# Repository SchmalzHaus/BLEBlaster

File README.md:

# BLEBlaster
Arduino/chipKIT OSHW shield with RN4678 BLE module from Microchip (plus 4 high power FETs)

Currently this repo is just a place for people to share the latest versions of the BLE Blaster files.

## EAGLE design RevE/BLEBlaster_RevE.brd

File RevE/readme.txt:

Guide for BLE Blaster Rev E shield

Please see the BLE Blaster Rev E Guide PDF file to see where each of the following features lies on the board.

SW Switch:

The SW Switch, which was a simple push button in the schematic and BOM, has been replaced on the boards with a slide switch. When the switch is pushed to the right (towards the BLE module) the module will be awake. When it is pushed to the left (away from the BLE module) it will be asleep.

High Powered FETs:

There are four high power FETs on the left hand side of the board. They take power from the FET Power Input screw terminals, and switch the positive power input to GND. Eaceh of the four output screw terminal blocks has to output terminals - a positive (unswiched) and a return (switched). The positive terminals are all connected together, and are also connected to the FET Power Input + input terminal. The terminals labeled 5, 6, 9, and 10 (on the silk screen) are switched to GND by the FETs, and are controlled by Arduino digital pins with the number given by the label. All of these pins are hardware PWM outputs on both Arduinos and chipKITs, so you can use this to do LED dimming or motor speed control, etc. There are through hole spots for BEMF diodes (D9, D9, D10 and D11) to be soldered in, but they are not populated by default. They would be used if any of the FET outputs had an inductive load like a relay or motor attached. 

Prototyping Area:

There are a few holes for prototyping circuits. There are some GND, 5V (if available), and 3.3V holes allong the bottom edge of the prototyping area.

3.3V Power LED (Green):

When lit, this LED indicates the presense of 3.3V on the board.

Connection LED (Red):

This LED is controlled by the BLE module, and has different meanings depending on the mode the BLE module is in. See BLE module datasheet for more information.

UART Connector:

This connector contains GND, 3.3V, TX, RX, CTS and RTS, and is pinned out for the MCP2200 module. It allows a direction connection to the BLE module should you want to communicate with it directly from a PC rather than going through a chipKIT or Arduino board.

Wakeup Button, Reset Button:

These are push buttons used by the BLE module. See the BLE module datasheet for more information.

System Mode Selection Jumpers:

This is a block of 9 pins. The left hand colum of 3 pins is all connected to +3.3V, the right hand column to GND, and the center column is connected to the P2_0, P2_4, and EAN pins of the BLE module. You would place jumpers across these pins to set the logic levels of thes three BLE module pins on boot to enter special firmware programming modes, for example. Note that no jumpers need to be connected to run normally, as the BLE module handles pull ups/pull downs appropriately for these three I/O pins.

Reset Enable Jumper:

Normally this jumper is not connected. But if you want to control the BLE module's reset pin from an Arduino/chipKIT pin (A5) then connect this jumper.

Voltage Select Jjumper:

This jumper needs to be connected. The left two pins should be shorted together if a 3.3V Arduino/chipKIT board is used, and the right to pins should be shorted if a 5V board is used. This simply sets the high-side voltage level of the level converters for TX, RX, P1_5 and P0_4.

I/O Enable Jumpers:

This is a block of 6 pairs of pins. Each of the 6 pins on the left (8, SDA, SCL, 7, 4, 13) can be shorted across to the pins on the right (WKUP, P1_3, P1_2, P0_4, P1_5 and SW_BTN) if so desired. The left hand column are Arduino/chipKIT pin names, and the right hand column are BLE module pin names. This jumper block allows any of the available BLE module pins to be connected to Arduino/chipKIT pins. None of these jumpers need to be connected by default - they are all optional.

RX Jumpers/TX Jumpers:

Each of these is a block of 4 sets of pins. On the left of each block are four different Arduino/chipKIT digital I/O pins, and the right hand column is all connected together, and goes to either the RX or TX level shifters and then on to the BLE module. These blocks are where you select which UART (or set of pins on the Arduino/chipKIT interface) the BLE modules connects to. For example, if you want the BLE module to connect to the standard Arduino hardware serial on pins 0 and 1, then you would put shorting jumpers across the bottom two pins of each of the blocks. You can move the jumpers up or down the blocks to select different TX or RX connections from the BLE module to the Arduino/chipKIT board. This allows for maximum flexibility when using the BLE Blaster shield, as you can avoid using UARTs that are already used for other purposes on your project.

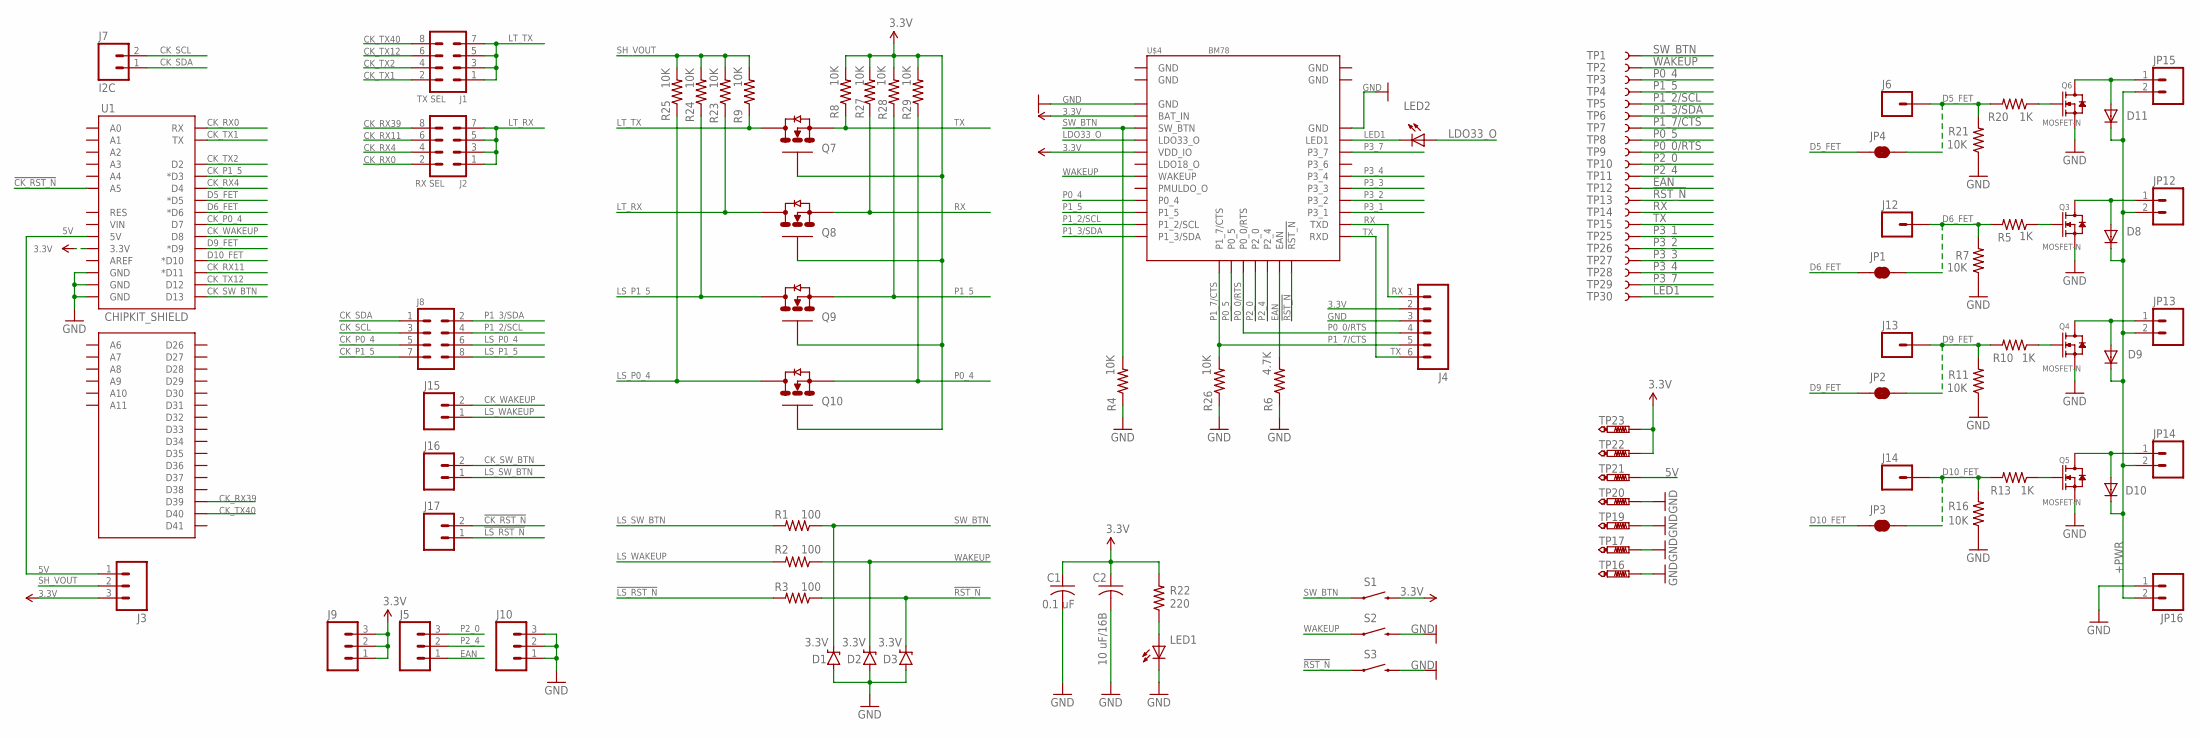
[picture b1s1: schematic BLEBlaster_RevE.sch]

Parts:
C1: 0.1 uF; C0603
C2: 10 uF/16B; C0805K
D1, D2, D3: 3.3V; SOD-323
D8, D9, D10, D11: DIODE-D-2.5; D-2.5
J1: TX SEL; 2X4
J2: RX SEL; 2X4
J3: M03PTH; 1X03
J4: M06SILK_FEMALE_PTH; 1X06
J5, J9, J10: M031X03_NO_SILK; 1X03_NO_SILK
J6, J12, J13, J14: M01PTH; 1X01
J7: I2C; 1X02_NO_SILK
J8: M04X2; 2X4
J15, J16, J17: M02PTH; 1X02
JP1, JP2, JP3, JP4: JUMPER-PAD-2-NC_BY_TRACE; PAD-JUMPER-2-NC_BY_TRACE_YES_SILK
JP12, JP13, JP14, JP15, JP16: M023.5MM; SCREWTERMINAL-3.5MM-2
LED1, LED2: LEDCHIPLED_0603; CHIPLED_0603
Q3, Q4, Q5, Q6: MOSFET-N; SOT-23
Q7, Q8, Q9, Q10: BSS138; SOT23
R1, R2, R3: 100; R0603
R4, R7, R8, R9, R11, R16, R21, R23, R24, R25, R26, R27, R28, R29: 10K; R0603
R5, R10, R13, R20: 1K; R0603
R6: 4.7K; R0603
R22: 220; R0603
S1, S2, S3: SWITCH-MOMENTARY-2SMD-4.6X2.8MM; TACTILE_SWITCH_SMD_4.6X2.8MM
TP1, TP2, TP3, TP4, TP5, TP6, TP7, TP8, TP9, TP10, TP11, TP12, TP13, TP14, TP15, TP25, TP26, TP27, TP28, TP29, TP30: TEST-POINT3X5; PAD.03X.05
TP16: 2 Pin Male Header, shared with TP24; P1-13
TP17, TP19, TP20, TP21, TP22, TP23: DNP; P1-13
U1: CHIPKIT_SHIELD; CHIPKIT_SHIELD_NOSILK
U$1: CHIPKIT2MM; CHIPKIT_2MM
U$2: ROHS_GARBAGE; ROHS_GARBAGE_5MM
U$3: CE_MARK5MM; CE_5MM
U$4: BM78; BM78SPPS5MC2/NC2

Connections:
3.3V: C1.1, C2.1, J3.3, J4.2, J9.1, J9.2, J9.3, Q7.1 (G), Q8.1 (G), Q9.1 (G), Q10.1 (G), R8.2, R22.2, R27.2, R28.2, R29.2, S1.3 (2), S1.4 (2), TP22.TP, TP23.TP, U1.3.3V, U$4.P4 (BAT_IN), U$4.P7 (VDD_IO)
5V: J3.1, TP21.TP, U1.5V
!CK_RST_N!: J17.2, U1.A5
!LS_RST_N!: J17.1, R3.2
!RST_N!: D3.C, R3.1, S3.1, S3.2 (1), TP13.P$1, U$4.P21 (!RST_N!)
+PWR: D8.C, D9.C, D10.C, D11.C, JP12.2, JP13.2, JP14.2, JP15.2, JP16.2
CK_P0_4: J8.5, U1.D7
CK_P1_5: J8.7, U1.D3 (*D3)
CK_RX0: J2.2, U1.RX
CK_RX4: J2.4, U1.D4
CK_RX11: J2.6, U1.D11 (*D11)
CK_RX39: J2.8, U1.D39
CK_SCL: J7.2, J8.3
CK_SDA: J7.1, J8.1
CK_SW_BTN: J16.2, U1.D13
CK_TX1: J1.2, U1.TX
CK_TX2: J1.4, U1.D2
CK_TX12: J1.6, U1.D12
CK_TX40: J1.8, U1.D40
CK_WAKEUP: J15.2, U1.D8
D5_FET: JP4.1, U1.D5 (*D5)
D5_FET_: J6.1, JP4.2, R20.2, R21.2
D6_FET: JP1.1, U1.D6 (*D6)
D6_FET_: J12.1, JP1.2, R5.2, R7.2
D9_FET: JP2.1, U1.D9 (*D9)
D9_FET_: J13.1, JP2.2, R10.2, R11.2
D10_FET: JP3.1, U1.D10 (*D10)
D10_FET_: J14.1, JP3.2, R13.2, R16.2
EAN: J5.1, R6.2, TP12.P$1, U$4.P20 (EAN)
GND: C1.2, C2.2, D1.A, D2.A, D3.A, J4.3, J10.1, J10.2, J10.3, JP16.1, LED1.C, Q3.2 (S), Q4.2 (S), Q5.2 (S), Q6.2 (S), R4.1, R6.1, R7.1, R11.1, R16.1, R21.1, R26.1, S2.3 (2), S2.4 (2), S3.3 (2), S3.4 (2), TP16.TP, TP17.TP, TP19.TP, TP20.TP, U1.GND@0 (GND), U1.GND@1 (GND), U1.GND@2 (GND), U$4.P1 (GND), U$4.P2 (GND), U$4.P3 (GND), U$4.P31 (GND), U$4.P32 (GND), U$4.P33 (GND)
LDO18_O: U$4.P8 (LDO18_O)
LDO33_O: LED2.A, U$4.P6 (LDO33_O)
LED1: LED2.C, TP30.P$1, U$4.P30 (LED1)
LS_P0_4: J8.6, Q10.3 (D), R25.1
LS_P1_5: J8.8, Q9.3 (D), R24.1
LS_SW_BTN: J16.1, R1.2
LS_WAKEUP: J15.1, R2.2
LT_RX: J2.1, J2.3, J2.5, J2.7, Q8.3 (D), R23.1
LT_TX: J1.1, J1.3, J1.5, J1.7, Q7.3 (D), R9.1
unnamed: Q3.1 (G), R5.1
unnamed: Q4.1 (G), R10.1
unnamed: Q5.1 (G), R13.1
unnamed: Q6.1 (G), R20.1
unnamed: D11.A, JP15.1, Q6.3 (D)
unnamed: D10.A, JP14.1, Q5.3 (D)
unnamed: LED1.A, R22.1
unnamed: D9.A, JP13.1, Q4.3 (D)
unnamed: D8.A, JP12.1, Q3.3 (D)
P0_0/RTS: J4.4, TP9.P$1, U$4.P17 (P0_0/RTS)
P0_4: Q10.2 (S), R29.1, TP3.P$1, U$4.P11 (P0_4)
P0_5: TP8.P$1, U$4.P16 (P0_5)
P1_2/SCL: J8.4, TP5.P$1, U$4.P13 (P1_2/SCL)
P1_3/SDA: J8.2, TP6.P$1, U$4.P14 (P1_3/SDA)
P1_5: Q9.2 (S), R28.1, TP4.P$1, U$4.P12 (P1_5)
P1_7/CTS: J4.5, R26.2, TP7.P$1, U$4.P15 (P1_7/CTS)
P2_0: J5.3, TP10.P$1, U$4.P18 (P2_0)
P2_4: J5.2, TP11.P$1, U$4.P19 (P2_4)
P3_1: TP25.P$1, U$4.P24 (P3_1)
P3_2: TP26.P$1, U$4.P25 (P3_2)
P3_3: TP27.P$1, U$4.P26 (P3_3)
P3_4: TP28.P$1, U$4.P27 (P3_4)
P3_7: TP29.P$1, U$4.P29 (P3_7)
PMULDO_O: U$4.P10 (PMULDO_O)
RX: J4.1, Q8.2 (S), R27.1, TP14.P$1, U$4.P23 (TXD)
SH_VOUT: J3.2, R9.2, R23.2, R24.2, R25.2
SW_BTN: D1.C, R1.1, R4.2, S1.1, S1.2 (1), TP1.P$1, U$4.P5 (SW_BTN)
TX: J4.6, Q7.2 (S), R8.1, TP15.P$1, U$4.P22 (RXD)
WAKEUP: D2.C, R2.1, S2.1, S2.2 (1), TP2.P$1, U$4.P9 (WAKEUP)

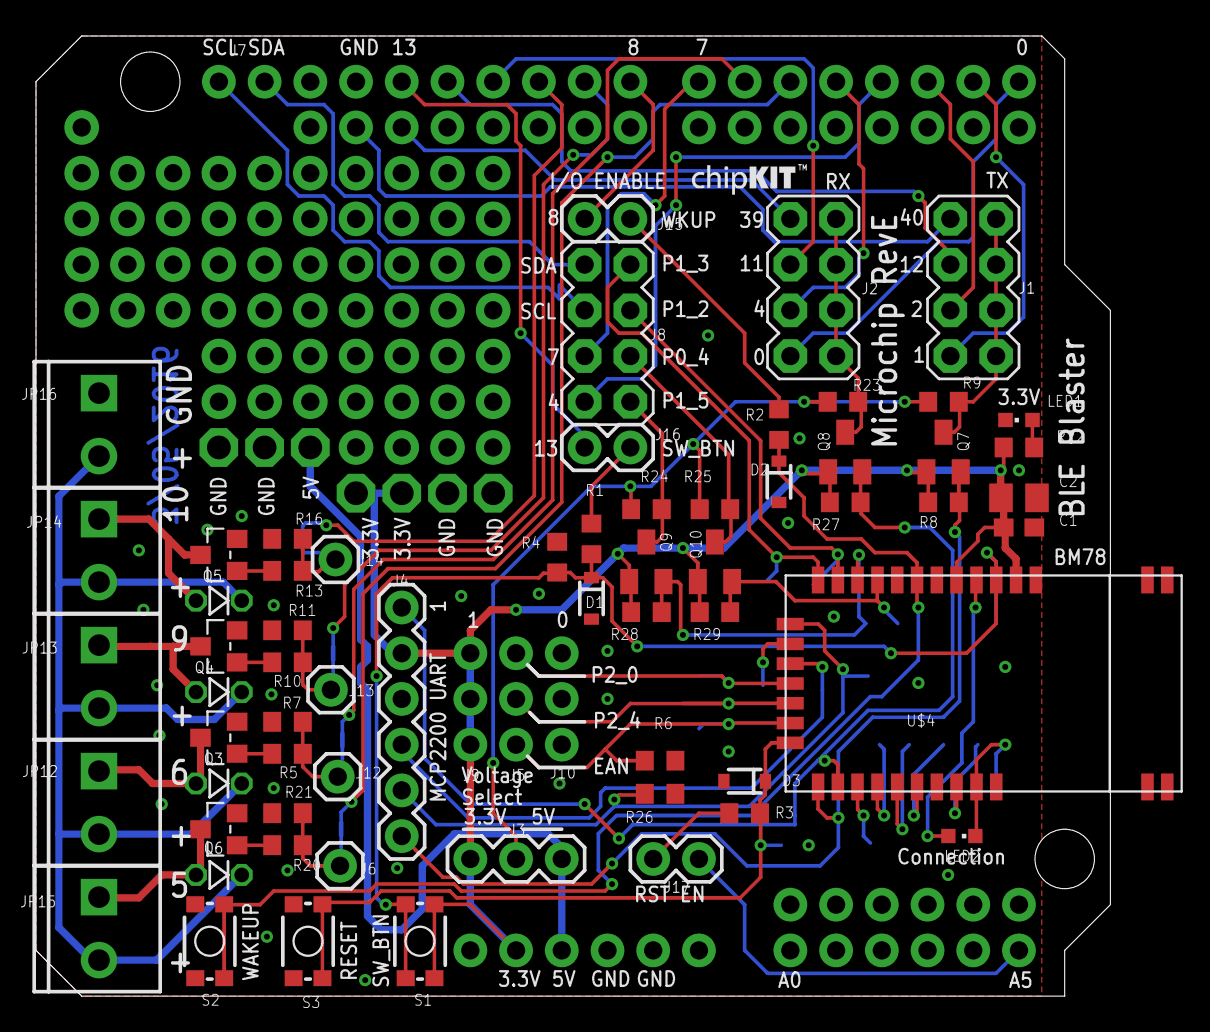
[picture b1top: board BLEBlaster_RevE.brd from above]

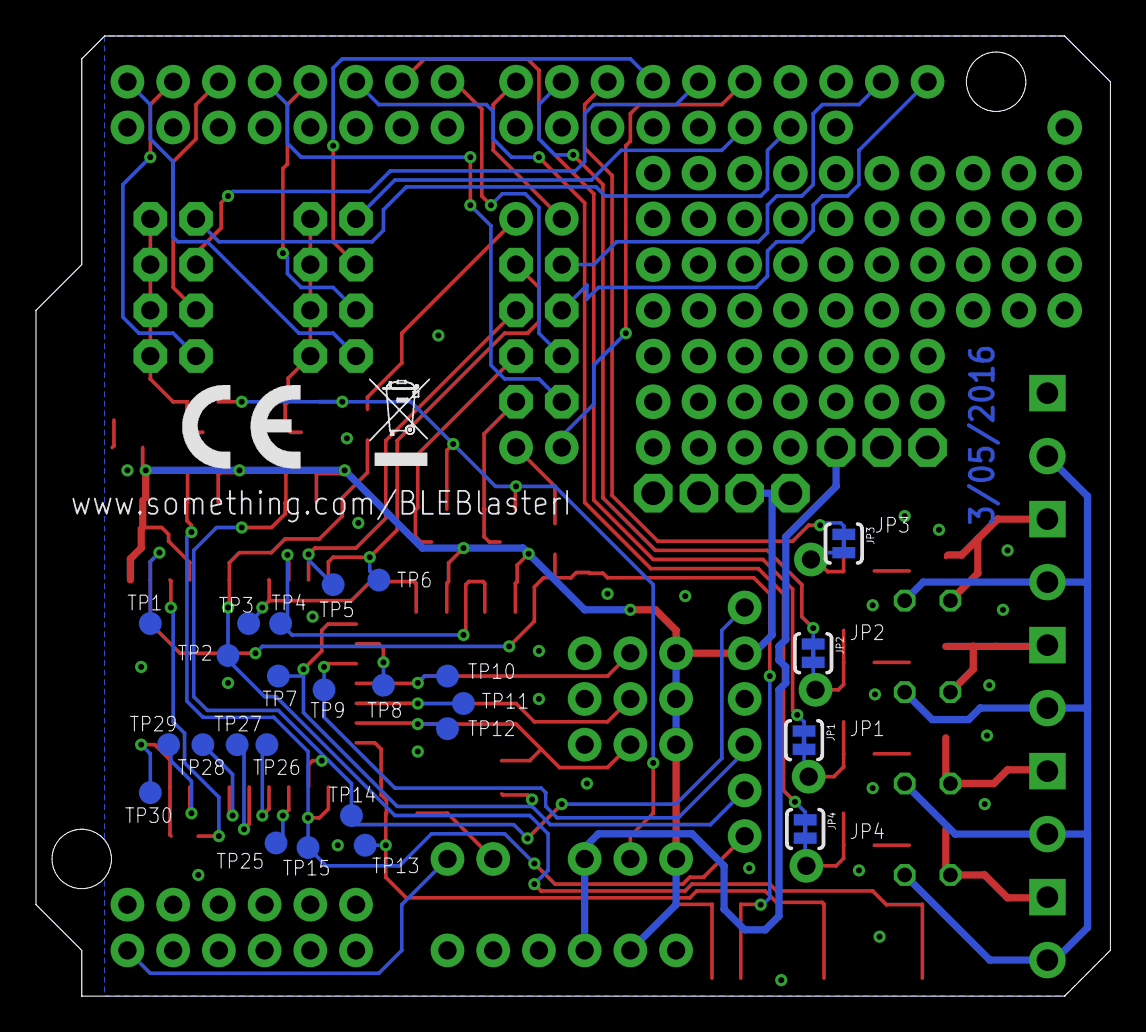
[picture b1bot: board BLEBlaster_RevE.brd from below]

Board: 2 copper layers, 59.7 x 53.3 mm, 103 parts (27 on the bottom side), 66 nets.

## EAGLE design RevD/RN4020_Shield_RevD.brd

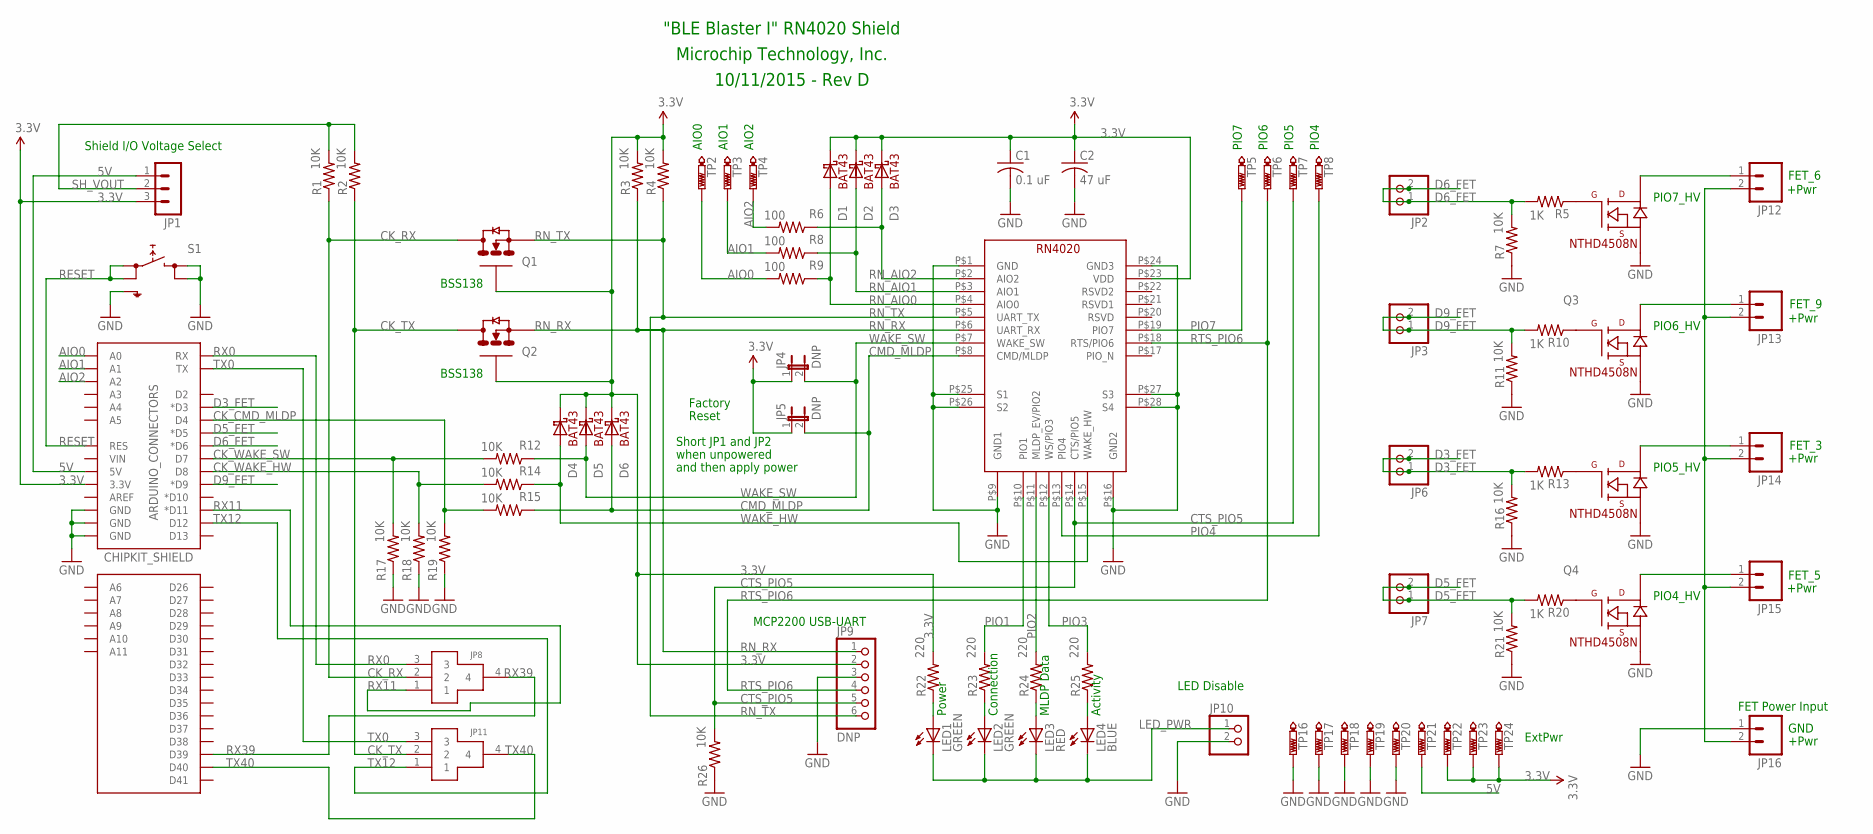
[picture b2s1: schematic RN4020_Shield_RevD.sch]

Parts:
ARDUINO_CONNECTORS: CHIPKIT_SHIELD
C1: 0.1 uF; C0805K
C2: 47 uF; C0805K
D1, D2, D3, D4, D5, D6: BA43; SOD123
JP1: 3 Pin Male Header; MA03-1
JP2, JP3, JP6, JP7: DNP; 1X02
JP4, JP5: DNP; SJ_2S-NO
JP8, JP11: 4PIN_3_WAY; 4_PIN_3_WAY
JP9: DNP; 1X06
JP10: 2 Pin Male Header; 1X02
JP12, JP13, JP14, JP15, JP16: M023.5MM; SCREWTERMINAL-3.5MM-2
LED1, LED2: GREEN; CHIP-LED0805
LED3: RED; CHIP-LED0805
LED4: BLUE; CHIP-LED0805
Q1, Q2: BSS138; SOT23
Q3, Q4: NTHD4508N; 1206A_8
R1, R2, R3, R4, R7, R11, R12, R14, R15, R16, R17, R18, R19, R21, R26: 10K; R0805W
R5, R10, R13, R20: 1K; R0805W
R6, R8, R9: 100; R0805W
R22, R23, R24, R25: 220; R0805W
S1: SKHMPSE010; SKHMPXE010
TP2, TP3, TP4, TP5, TP6, TP7, TP8, TP17, TP18, TP19, TP20, TP21, TP22, TP23: DNP; P1-13
TP16: 2 Pin Male Header, shared with TP24; P1-13
TP24: 2 Pin Male Header shared with TP16; P1-13
U1: RN4020

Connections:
3.3V: ARDUINO_CONNECTORS.3.3V, C1.1, C2.1, D1.C, D2.C, D3.C, D4.C, D5.C, D6.C, JP1.3, JP4.1, JP5.1, JP9.2, Q1.1 (G), Q2.1 (G), R3.2, R4.2, R22.2, TP22.TP, TP23.TP, TP24.TP, U1.P$23 (VDD)
5V: ARDUINO_CONNECTORS.5V, JP1.1, TP21.TP
AIO0: ARDUINO_CONNECTORS.A0, R9.2, TP2.TP
AIO1: ARDUINO_CONNECTORS.A1, R8.2, TP3.TP
AIO2: ARDUINO_CONNECTORS.A2, R6.2, TP4.TP
CK_CMD_MLDP: ARDUINO_CONNECTORS.D4, R15.2, R19.2
CK_RX: JP8.2, Q1.3 (D), R1.1
CK_TX: JP11.2, Q2.3 (D), R2.1
CK_WAKE_HW: ARDUINO_CONNECTORS.D8, R14.2, R18.2
CK_WAKE_SW: ARDUINO_CONNECTORS.D7, R12.2, R17.2
CMD_MLDP: D6.A, JP5.2, R15.1, U1.P$8 (CMD/MLDP)
CTS_PIO5: JP9.5, R26.2, TP7.TP, U1.P$14 (CTS/PIO5)
D3_FET: ARDUINO_CONNECTORS.D3 (*D3), JP6.1, JP6.2, R13.2, R16.2
D5_FET: ARDUINO_CONNECTORS.D5 (*D5), JP7.1, JP7.2, R20.2, R21.2
D6_FET: ARDUINO_CONNECTORS.D6 (*D6), JP2.1, JP2.2, R5.2, R7.2
D9_FET: ARDUINO_CONNECTORS.D9 (*D9), JP3.1, JP3.2, R10.2, R11.2
GND: ARDUINO_CONNECTORS.GND@0 (GND), ARDUINO_CONNECTORS.GND@1 (GND), ARDUINO_CONNECTORS.GND@2 (GND), C1.2, C2.2, JP9.3, JP10.2, JP16.1, Q3.S1 (S2), Q3.S2 (S1), Q4.S1 (S2), Q4.S2 (S1), R7.1, R11.1, R16.1, R17.1, R18.1, R19.1, R21.1, R26.1, S1.3 (2.1), S1.4 (2.2), S1.5 (SH), TP16.TP, TP17.TP, TP18.TP, TP19.TP, TP20.TP, U1.P$1 (GND), U1.P$9 (GND1), U1.P$16 (GND2), U1.P$24 (GND3), U1.P$25 (S1), U1.P$26 (S2), U1.P$27 (S3), U1.P$28 (S4)
LED_PWR: JP10.1, LED1.C, LED2.C, LED3.C, LED4.C
unnamed: Q4.G1 (G2), R13.1
unnamed: LED4.A, R25.1
unnamed: LED2.A, R23.1
unnamed: LED3.A, R24.1
unnamed: Q4.G2 (G1), R20.1
unnamed: Q3.G2 (G1), R10.1
unnamed: Q3.G1 (G2), R5.1
unnamed: JP12.2, JP13.2, JP14.2, JP15.2, JP16.2
unnamed: JP12.1, Q3.D1 (D2)
unnamed: JP13.1, Q3.D2 (D1)
unnamed: LED1.A, R22.1
unnamed: JP14.1, Q4.D1 (D2)
unnamed: JP15.1, Q4.D2 (D1)
PIO1: R23.2, U1.P$10 (PIO1)
PIO2: R24.2, U1.P$11 (MLDP_EV/PIO2)
PIO3: R25.2, U1.P$12 (WS/PIO3)
PIO4: TP8.TP, U1.P$13 (PIO4)
PIO7: TP5.TP, U1.P$19 (PIO7)
RESET: ARDUINO_CONNECTORS.RES, S1.1 (1.1), S1.2 (1.2)
RN_AIO0: D1.A, R9.1, U1.P$4 (AIO0)
RN_AIO1: D2.A, R8.1, U1.P$3 (AIO1)
RN_AIO2: D3.A, R6.1, U1.P$2 (AIO2)
RN_RX: JP9.1, Q2.2 (S), R3.1, U1.P$6 (UART_RX)
RN_TX: JP9.6, Q1.2 (S), R4.1, U1.P$5 (UART_TX)
RTS_PIO6: JP9.4, TP6.TP, U1.P$18 (RTS/PIO6)
RX0: ARDUINO_CONNECTORS.RX, JP8.3
RX11: ARDUINO_CONNECTORS.D11 (*D11), JP8.1
RX39: ARDUINO_CONNECTORS.D39, JP8.4
SH_VOUT: JP1.2, R1.2, R2.2
TX0: ARDUINO_CONNECTORS.TX, JP11.3
TX12: ARDUINO_CONNECTORS.D12, JP11.1
TX40: ARDUINO_CONNECTORS.D40, JP11.4
WAKE_HW: D4.A, R14.1, U1.P$15 (WAKE_HW)
WAKE_SW: D5.A, JP4.2, R12.1, U1.P$7 (WAKE_SW)

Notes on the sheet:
BSS138
PIO4
PIO5
PIO6
PIO7
AIO2
AIO1
AIO0
Factory
Reset
Short JP1 and JP2
and then apply power
when unpowered
"BLE Blaster I" RN4020 Shield
Microchip Technology, Inc.
10/11/2015 - Rev D
PIO4_HV
PIO5_HV
PIO6_HV
PIO7_HV
MCP2200 USB-UART
Shield I/O Voltage Select
LED Disable
Power
Connection
MLDP Data
Activity
ExtPwr
FET Power Input
+Pwr
GND
FET_6
FET_9
FET_3
FET_5

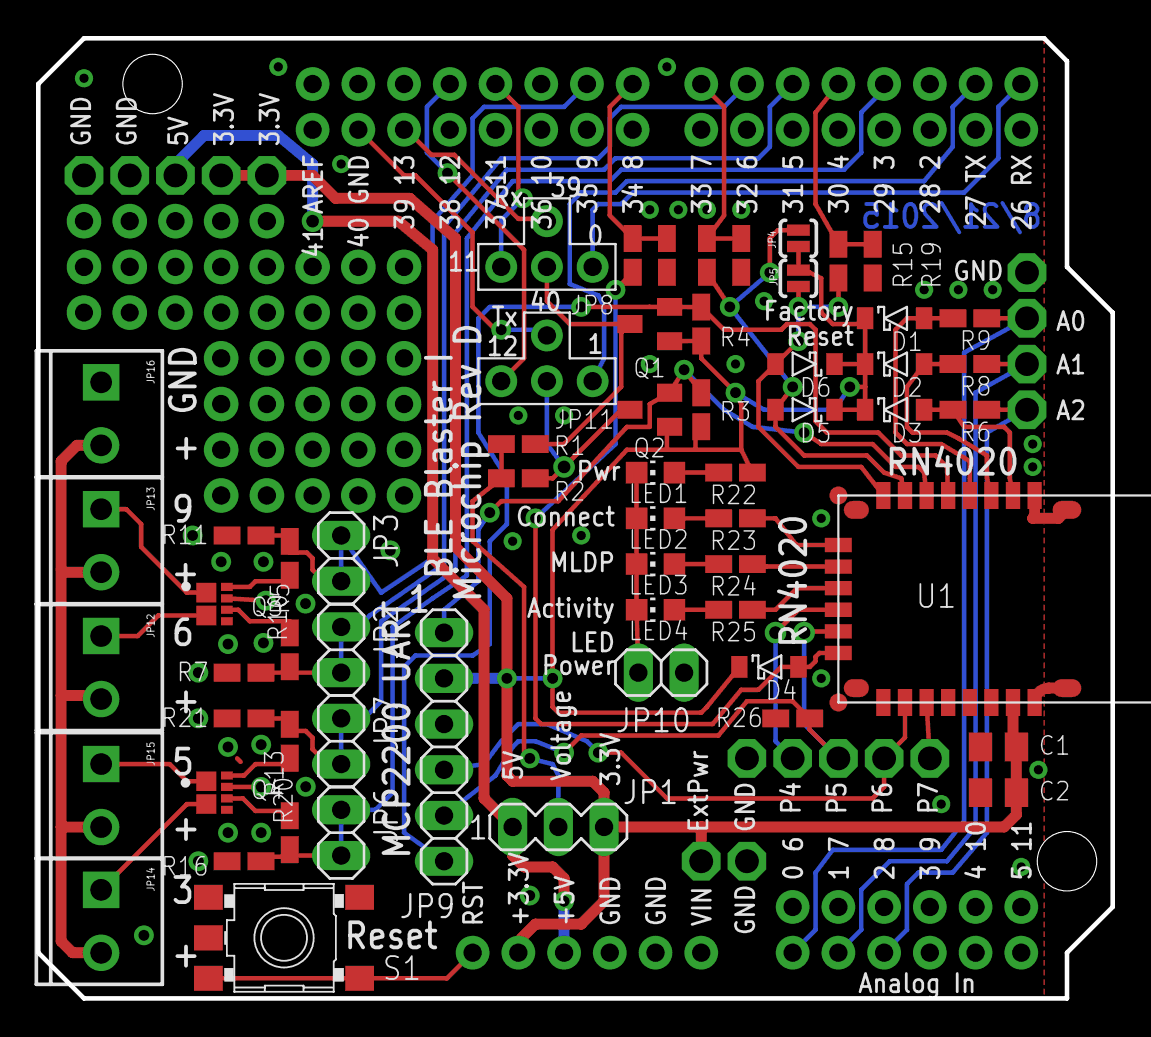
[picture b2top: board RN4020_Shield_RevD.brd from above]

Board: 2 copper layers, 59.7 x 53.3 mm, 77 parts (0 on the bottom side), 52 nets.

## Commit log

2016-08-07 Initial check in of files that have been floating around in e-mails since this project began.
2016-08-09 Added 'guide' documentation for explanations of each part of the board.

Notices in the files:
parts and their libraries:
SparkFun-Connectors: Licensing: Creative Commons ShareAlike 4.0 International - https://creativecommons.org/licenses/by-sa/4.0
